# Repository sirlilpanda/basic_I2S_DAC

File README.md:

# basic_I2S_DAC
A simple desgin for a I2S DAC with 24bit resolution and 192KHz sampling.

this was desgined to work a longside the [function generator](https://github.com/sirlilpanda/function-generator) as an expansion board for basic testing of I2S and usb audio devices.

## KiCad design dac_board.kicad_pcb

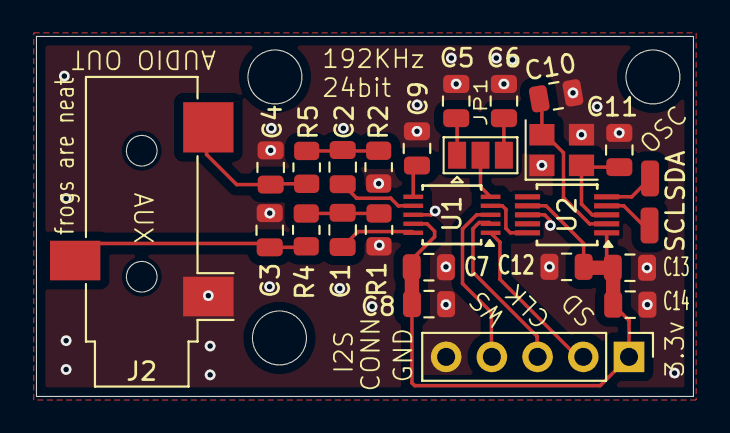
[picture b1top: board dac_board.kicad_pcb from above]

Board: 2 copper layers, 36.5 x 20.0 mm, 26 parts (0 on the bottom side), 20 nets.

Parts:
C1, C2, C5: 3.3u; C_0805_2012Metric
C3, C4: C; C_0805_2012Metric
C6: 10u; C_0805_2012Metric
C7, C8, C9, C12, C13: 0.1u; C_0805_2012Metric
C10, C11: 8p; C_0805_2012Metric
C14: 1u; C_0805_2012Metric
J1: Conn_01x05_Pin; PinHeader_1x05_P2.54mm_Vertical
J2: AudioJack3; Jack_3.5mm_CUI_SJ-3523-SMT_Horizontal
JP1: Popguard ramp; SolderJumper-3_P1.3mm_Open_Pad1.0x1.5mm
R1, R2: 10k; R_0805_2012Metric
R4, R5: 470; R_0805_2012Metric
SCL: TestPoint; SolderWirePad_1x01_SMD_1x2mm
SDA: TestPoint; SolderWirePad_1x01_SMD_1x2mm
U1: CS4344; TSSOP-10_3x3mm_P0.5mm
U2: Si5351A-B-GT; MSOP-10_3x3mm_P0.5mm
Y1: 25MHz; Crystal_SMD_3225-4Pin_3.2x2.5mm

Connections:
+3.3V: C7.1, C8.1, C12.1, C13.1, C14.1, J1.1, U1.9 (VA), U2.1 (VDD), U2.7 (VDDO)
/I2S_CLK: J1.3, U1.2 (~DEM/SCLK)
/I2S_SD: J1.2, U1.1 (SDIN)
/I2S_WS: J1.4, U1.3 (LRCK)
/MCLK: U1.4 (MCLK), U2.10 (CLK0)
/OUT_L: C2.2, U1.7 (AOUTL)
/OUT_L_POST: C4.1, J2.T, R5.2
/OUT_R: C1.2, U1.10 (AOUTR)
/OUT_R_POST: C3.1, J2.R, R4.2
GND: C3.2, C4.2, C5.2, C6.2, C7.2, C8.2, C9.2, C10.1, C11.1, C12.2, C13.2, C14.2, J1.5, J2.S, R1.2, R2.2, U1.8 (GND), U2.8 (GND), Y1.1, Y1.3
unnamed: C1.1, R1.1, R4.1
unnamed: C2.1, R2.1, R5.1
unnamed: C5.1, JP1.1 (A)
unnamed: C6.1, JP1.3 (B)
unnamed: JP1.2 (C), U1.5 (VQ)
unnamed: C9.1, U1.6 (FILT+)
unnamed: SCL.1, U2.4 (SCL)
unnamed: SDA.1, U2.5 (SDA)
unnamed: C10.2, U2.2 (XA), Y1.4
unnamed: C11.2, U2.3 (XB), Y1.2
